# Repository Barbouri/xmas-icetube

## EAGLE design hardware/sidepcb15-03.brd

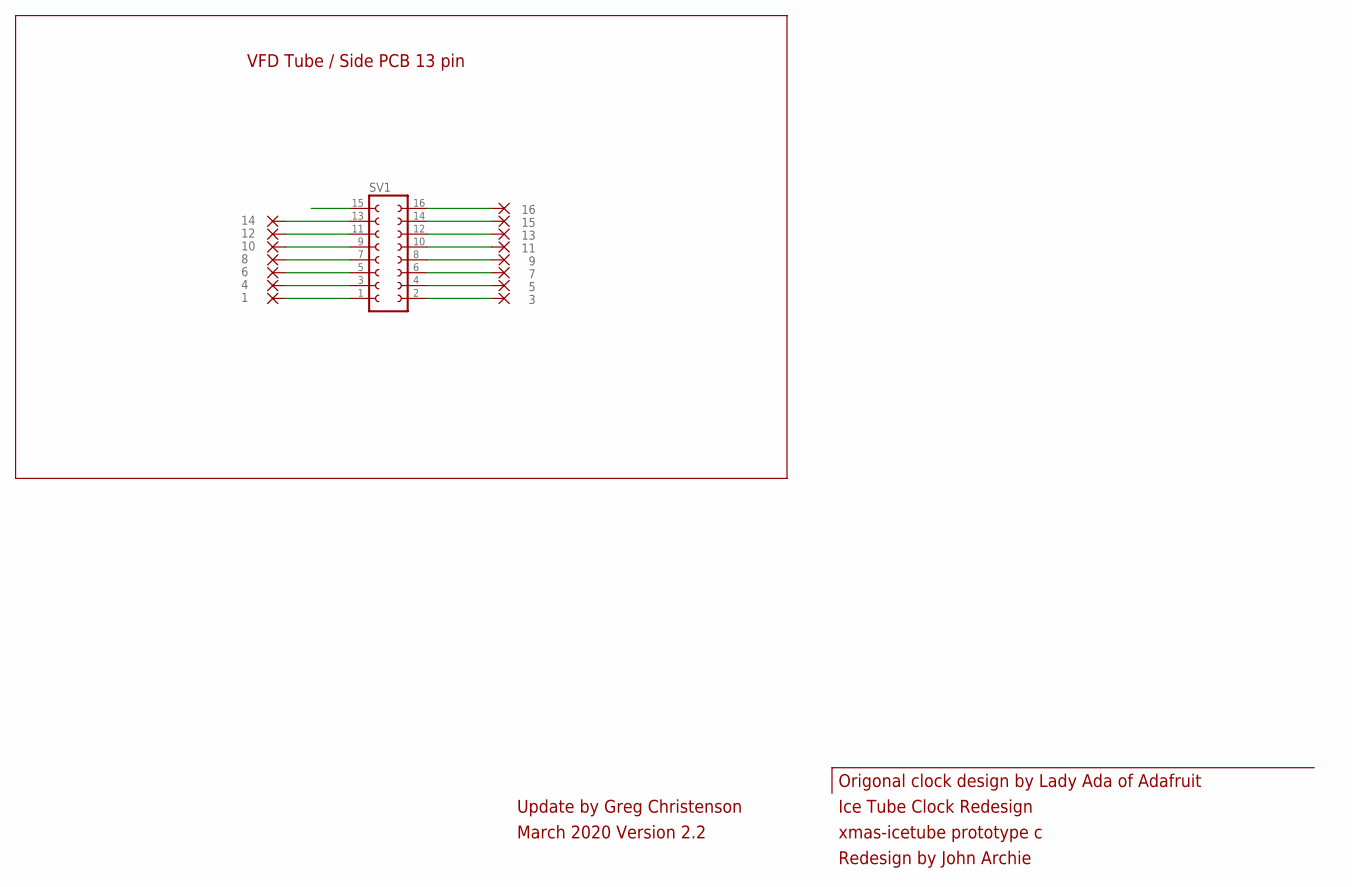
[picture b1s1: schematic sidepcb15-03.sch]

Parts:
1, 3, 4, 5, 6, 7, 8, 9, 10, 11, 12, 13, 14, 15, 16: 1,6/0,8
SV1: FE08-2W

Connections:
E-A,W: 3.1, SV1.2
E-B: 16.1, SV1.16
E-C,S: 13.1, SV1.12
E-D: 12.1, SV1.11
E-E: 14.1, SV1.13
E-F: 1.1, SV1.1
E-G,M: 15.1, SV1.14
E-P: 11.1, SV1.10
G8: 8.1, SV1.7
G9: 7.1, SV1.6
G10: 6.1, SV1.5
G11: 5.1, SV1.4
G13: 9.1, SV1.8
G14: 10.1, SV1.9
G-12: 4.1, SV1.3
GND: SV1.15

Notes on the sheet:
Ice Tube Clock Redesign
xmas-icetube prototype c
Redesign by John Archie
VFD Tube / Side PCB 13 pin
Origonal clock design by Lady Ada of Adafruit
Update by Greg Christenson
March 2020 Version 2.2

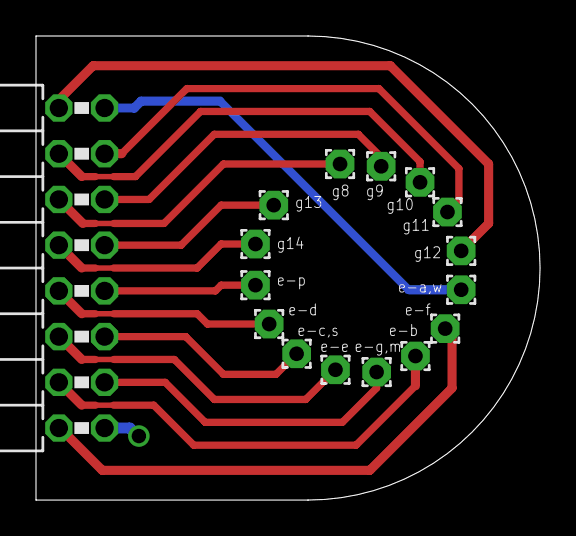
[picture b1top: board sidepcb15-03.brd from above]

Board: 2 copper layers, 28.0 x 25.8 mm, 16 parts (0 on the bottom side), 15 nets.

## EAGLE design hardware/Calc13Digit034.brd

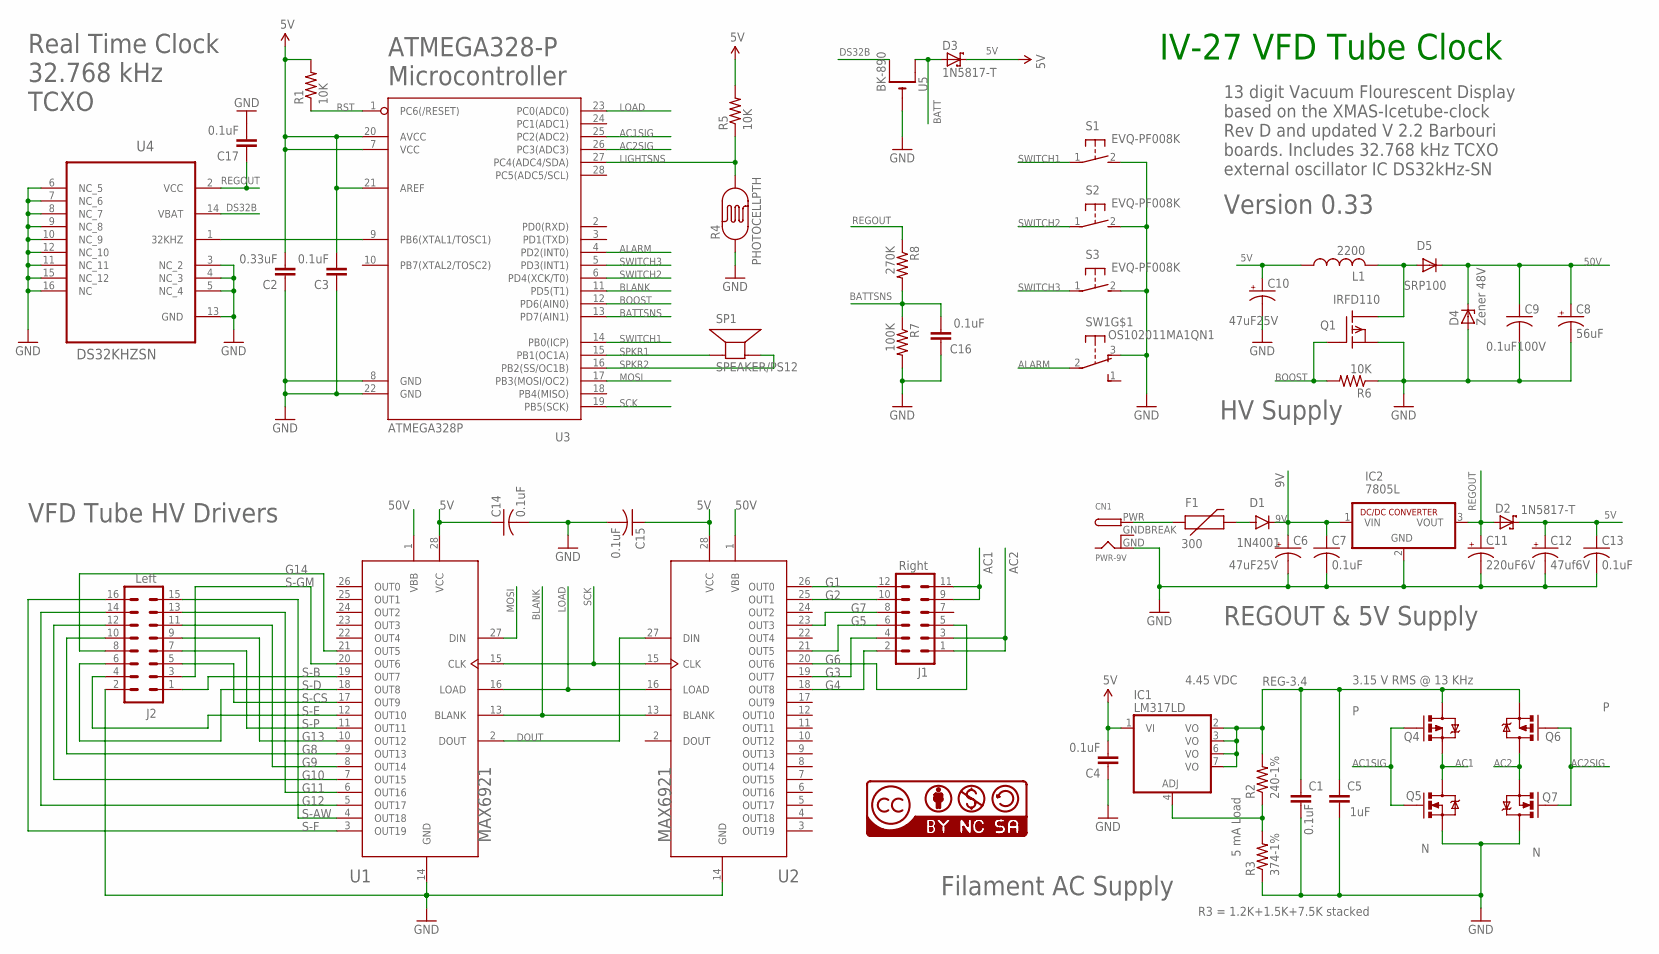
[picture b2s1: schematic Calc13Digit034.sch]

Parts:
C1, C3, C4, C16, C17: 0.1uF; 0603-CAP
C2: 0.33uF; 0603-CAP
C5: 1uF; 0603-CAP
C6, C10: 47uF25V; E2,5-7
C7: 0.1uF; C0805
C8: 56uF; E3,5-8
C9: 0.1uF100V; C025-024X044
C11: 220uF6V; E2,5-7
C12: 47uf6V; E2,5-7
C13, C14, C15: 0.1uF; C025-024X044
CN1: PWR-9V; DCJACK_2MM_PTH
D1: 1N4001; DIODE-1N4001
D2, D3: 1N5817-T; DO41-7.6
D4: Zener 48V; ZDIO-10
D5: SRP100; DO41-10
F1: 300; PTC
IC1: LM317LD; SO08
IC2: 7805L; SIP3
J1: Right; 2X6
J2: Left; 2X8
L1: 2200; 6000
Q1: IRFD110; DIL04
Q4, Q6: P; SOT23-3
Q5, Q7: N; SOT23-3
R1, R5, R6: 10K; 0603-RES
R2: 240-1%; 0805
R3: 374-1%; 0805
R4: PHOTOCELLPTH; PHOTOCELL
R7: 100K; 0603-RES
R8: 270K; 0603-RES
S1, S2, S3: EVQ-PF008K; B3F-31XX
SP1: SPEAKER/PS12; PS12
SW1: OS102011MA1QN1; OS102011MA1Q
U1, U2: MAX6921; PLCC-S28
U3: ATMEGA328P; DIL28-3
U4: DS32KHZSN; SOIC127P1034X267-16N
U5: BK-890; CR1220-THM
U$2: CC-NC-BCSMALL; CC-NC-BY_SMALL

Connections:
5V: C2.2, C3.2, C4.2, C10.+, C12.+, C13.1, C14.1, C15.1, D2.C, D3.C, IC1.1 (VI), L1.1, R1.2, R5.2, U1.28 (VCC), U2.28 (VCC), U3.7 (VCC), U3.20 (AVCC), U3.21 (AREF)
9V: C6.+, C7.1, D1.C, IC2.1 (VIN)
32KHZ: U3.9 (PB6(XTAL1/TOSC1)), U4.1 (32KHZ)
50V: C8.+, C9.1, D4.C, D5.C, U1.1 (VBB), U2.1 (VBB)
AC1: J1.9, J1.11, Q4.2 (S), Q5.3 (D)
AC1SIG: Q4.1 (G), Q5.1 (G), U3.25 (PC2(ADC2))
AC2: J1.1, J1.3, Q6.3 (D), Q7.2 (S)
AC2SIG: Q6.1 (G), Q7.1 (G), U3.26 (PC3(ADC3))
ALARM: SW1.2, U3.4 (PD2(INT0))
BATT: D3.A, U5.+1 (+)
BATTSNS: C16.2, R7.1, R8.2, U3.13 (PD7(AIN1))
BLANK: U1.13 (BLANK), U2.13 (BLANK), U3.11 (PD5(T1))
BOOST: Q1.1 (G), R6.2, U3.12 (PD6(AIN0))
DOUT: U1.2 (DOUT), U2.27 (DIN)
DS32B: U4.14 (VBAT), U5.+2 (+1)
F9V: D1.A, F1.P$2 (2)
G1: J1.12, U2.26 (OUT0)
G2: J1.10, U2.25 (OUT1)
G3: J1.4, U2.19 (OUT7)
G4: J1.2, U2.18 (OUT8)
G5: J1.6, U2.21 (OUT5)
G6: J1.5, U2.20 (OUT6)
G7: J1.8, U2.23 (OUT3)
G8: J2.10, U1.9 (OUT13)
G9: J2.11, U1.8 (OUT14)
G10: J2.12, U1.7 (OUT15)
G11: J2.13, U1.6 (OUT16)
G12: J2.14, U1.5 (OUT17)
G13: J2.9, U1.10 (OUT12)
G14: J2.8, U1.21 (OUT5)
GND: C1.1, C2.1, C3.1, C4.1, C5.1, C6.-, C7.2, C8.-, C9.2, C10.-, C11.-, C12.-, C13.2, C14.2, C15.2, C16.1, C17.2, CN1.GND, D4.A, IC2.2 (GND), J2.2, Q1.2 (S), Q5.2 (S), Q7.3 (D), R3.1, R4.1, R6.1, R7.2, S1.2 (S), S2.2 (S), S3.2 (S), SW1.3 (O), U1.14 (GND), U2.14 (GND), U3.8 (GND), U3.22 (GND), U4.3 (NC_2), U4.4 (NC_3), U4.5 (NC_4), U4.6 (NC_5), U4.7 (NC_6), U4.8 (NC_7), U4.9 (NC_8), U4.10 (NC_9), U4.11 (NC_11), U4.12 (NC_10), U4.13 (GND), U4.15 (NC_12), U4.16 (NC), U5.-
GNDBREAK: CN1.GNDBREAK
LIGHTSNS: R4.2, R5.1, U3.27 (PC4(ADC4/SDA))
LOAD: U1.16 (LOAD), U2.16 (LOAD), U3.23 (PC0(ADC0))
MOSI: U1.27 (DIN), U3.17 (PB3(MOSI/OC2))
unnamed: D5.A, L1.2, Q1.3 (D), Q1.4 (D)
unnamed: IC1.4 (ADJ), R2.1, R3.2
PWR: CN1.PWR, F1.P$1 (1)
REG-3.4: C1.2, C5.2, IC1.2 (VO), IC1.3 (VO), IC1.6 (VO), IC1.7 (VO), Q4.3 (D), Q6.2 (S), R2.2
REGOUT: C11.+, C17.1, D2.A, IC2.3 (VOUT), R8.1, U4.2 (VCC)
RST: R1.1, U3.1 (PC6(/RESET))
S-AW: J2.15, U1.4 (OUT18)
S-B: J2.1, U1.19 (OUT7)
S-CS: J2.5, U1.17 (OUT9)
S-D: J2.6, U1.18 (OUT8)
S-E: J2.4, U1.12 (OUT10)
S-F: J2.16, U1.3 (OUT19)
S-GM: J2.3, U1.20 (OUT6)
S-P: J2.7, U1.11 (OUT11)
SCK: U1.15 (CLK), U2.15 (CLK), U3.19 (PB5(SCK))
SPKR1: SP1.P$1 (+), U3.15 (PB1(OC1A))
SPKR2: SP1.P$2 (-), U3.16 (PB2(SS/OC1B))
SWITCH1: S1.1, U3.14 (PB0(ICP))
SWITCH2: S2.1, U3.6 (PD4(XCK/T0))
SWITCH3: S3.1, U3.5 (PD3(INT1))

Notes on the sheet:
IV-27 VFD Tube Clock
13 digit Vacuum Flourescent Display based on the XMAS-Icetube-clock Rev D and updated V 2.2 Barbouri boards. Includes 32.768 kHz TCXO external oscillator IC DS32kHz-SN
Version 0.33
REGOUT & 5V Supply
Filament AC Supply
VFD Tube HV Drivers
Real Time Clock 32.768 kHz TCXO
ATMEGA328-P Microcontroller
HV Supply
3.15 V RMS @ 13 KHz
4.45 VDC
5 mA Load
R3 = 1.2K+1.5K+7.5K stacked

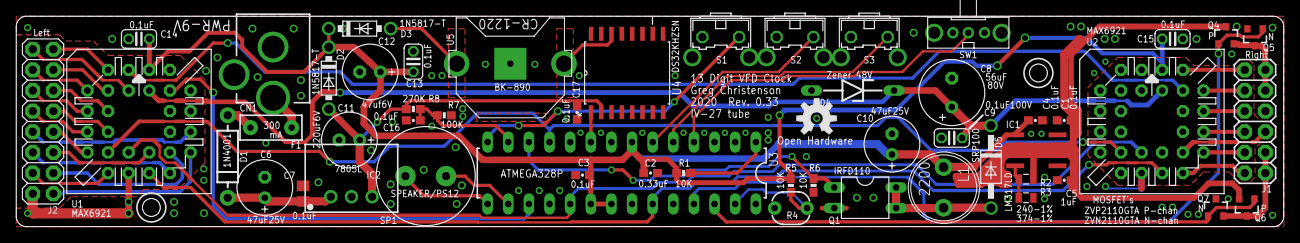
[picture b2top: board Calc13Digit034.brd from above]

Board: 2 copper layers, 156.1 x 25.9 mm, 54 parts (1 on the bottom side), 54 nets.

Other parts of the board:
U$1: OSHW-LOGO-M

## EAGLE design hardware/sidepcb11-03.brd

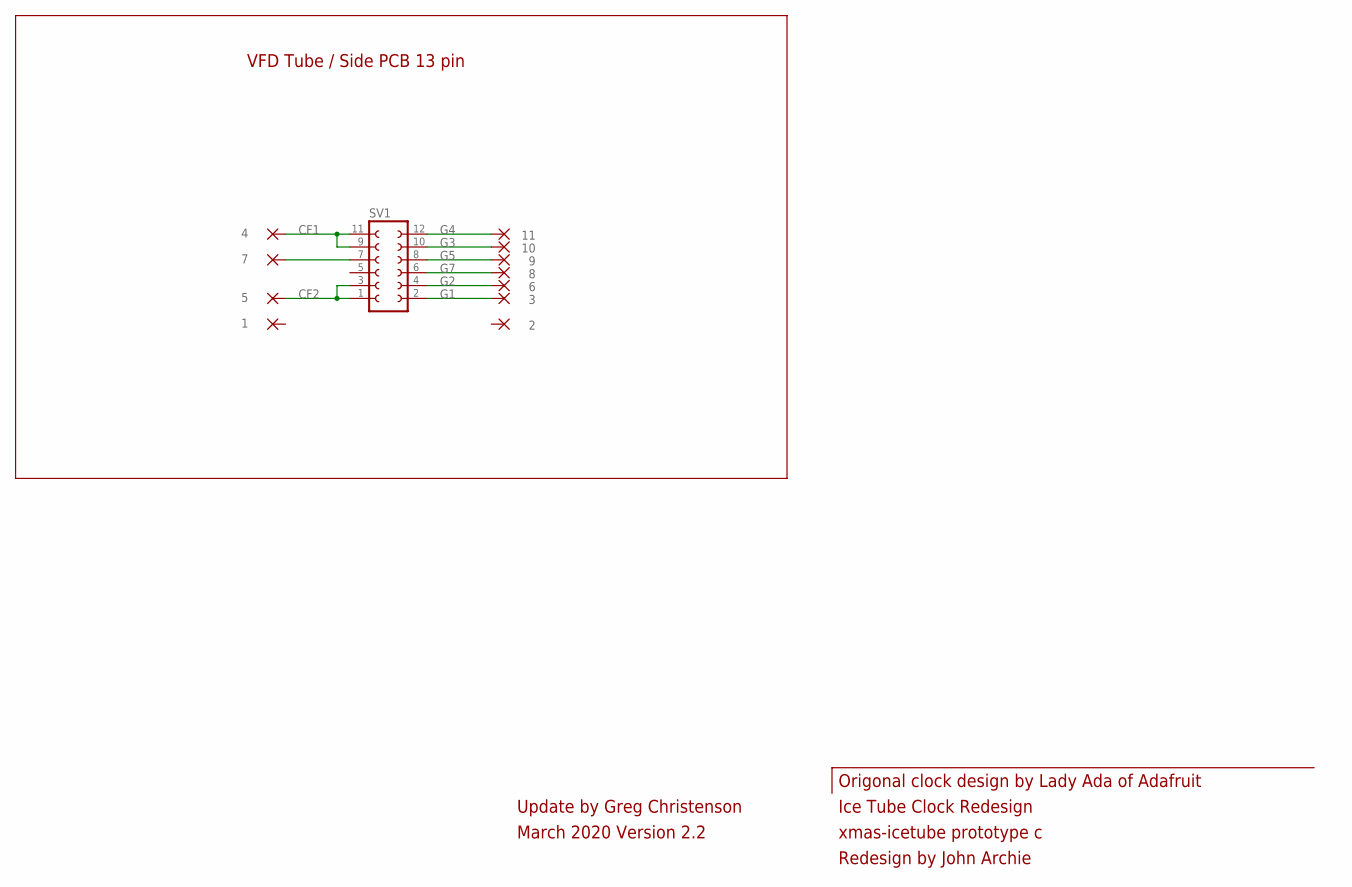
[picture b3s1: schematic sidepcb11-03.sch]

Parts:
1, 2, 3, 4, 5, 6, 7, 8, 9, 10, 11: 1,6/0,8
SV1: FE06-2W

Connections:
CF1: 4.1, SV1.9, SV1.11
CF2: 5.1, SV1.1, SV1.3
G1: 3.1, SV1.2
G2: 6.1, SV1.4
G3: 10.1, SV1.10
G4: 11.1, SV1.12
G5: 9.1, SV1.8
G6: 7.1, SV1.7
G7: 8.1, SV1.6

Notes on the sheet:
Ice Tube Clock Redesign
xmas-icetube prototype c
Redesign by John Archie
VFD Tube / Side PCB 13 pin
Origonal clock design by Lady Ada of Adafruit
Update by Greg Christenson
March 2020 Version 2.2

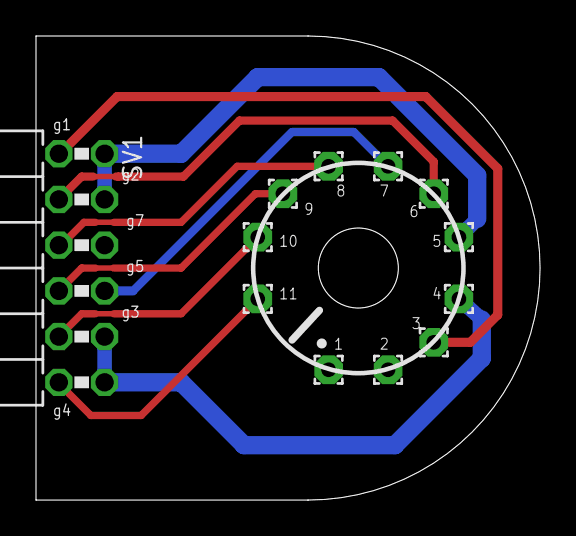
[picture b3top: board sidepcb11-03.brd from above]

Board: 2 copper layers, 28.0 x 25.8 mm, 12 parts (0 on the bottom side), 9 nets.

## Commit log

2020-05-18 Added IV-27 13 digit VFD tube PCB files
    PCB files for 13-digit IV-27 VFD tube version of Icetube clock.
    Eagle 7.7 format BRD and SCH files. Mainboard version 3.4

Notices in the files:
parts and their libraries:
SparkFun-Connectors: Licensing: Creative Commons ShareAlike 4.0 International - https://creativecommons.org/licenses/by-sa/4.0
cc-by-nc-sa: All hardware is licensed under the Creative Commons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
